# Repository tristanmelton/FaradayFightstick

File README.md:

### FaradayFightstick
Utilize Hall Effect sensors in an open-source leverless.

Use an ATMEGA microcontroller to read the analog out from the hall effect sensor located on the opposite side of the PCB from the switch. Then, the ATMEGA will act as the switch and output high or low to a Brooks board for each button press.

There are board versions for a RP2040, Brooks P5 Mini and Brooks Gen-5X Mini. I have tested the RP2040 and P5 Mini versions and they both work on PC.
## Setup
The board is relatively simple to set up - the most difficult part was soldering the USB-C for the ATMEGA32u4. I have no reflow oven so I used my conventional oven with solder paste, which works but is a little difficult to get the timing right to not melt the plastic in the connector.

Once all components are soldered, burn the Arduino bootloader with the "Arduino as ISP" option with an Arduino Uno or equivalent, or another bootloader burner, connected to the ICSP headers on the ATMEGA32u4 which are broken out for convenience, set to an Arduino Micro as the target. Then, plug in the USB-C and upload the ADC.ino sketch.

Once uploaded, unplug and hold LP while plugging back in and run the configurator python script (to be wrapped into an exe later). It should automatically detect the controller. If not, select the COM port corresponding to your board (should say COMXX: Arduino Micro), and click Connect. The progress bar will fill as the default values are read from memory. Set the values using the sliders and click "Submit New Thresholds". Wait for the progress bar to fill and then you can unplug.

Unplug from the ATMEGA side and plug the controller into your computer. If using the RP2040 board, upload the GP2040-CE firmware. Once done, you should be good to go!

There is compatibility for a MagicBoots with the RP2040 board but I have not tested it nor the P5 mini or Gen-5X versions as I don't own a PS5. Always open to donations :)
## TODO
- [ ] Test the P5 Mini version on a PS5.
- [x] Add an "unpressed" level so users have an idea of what range of value to put in
- [x] Add a diode on the voltage input from each USB socket to prevent backflow of current to the host PC and damaging it

## Changelog
# v1.1 (5/5/2025)
- Added boards for P5 mini and Gen-5X mini
- Added current-blocking diodes to prevent blowing up your USB if plugged into both USB ports at the same time
- Updated ADC firmware to support additional commands:
  - GETALLVAL;: get all current button values.
  - GETALLTRIG;: get all trigger threshold levels.
  - GETTRIG;XX: get a singular trigger threshold from memory.  XX indicates the memory offset to read from.
  - LP;X, MP;X, HP;X, SHP;X,...: Sets the trigger threshold value to X in absolute units.
- Updated interface software to use sliders from 100 to 0 to set the sensitivity. 100 is max sensitivity, 0 is no sensitivity.
- Software will try and auto-detect the controller when plugged in. 
# v1.0 (3/6/2025)
The leverless is working! I wrote a quick interface with Python to read and write button trigger thresholds to the EEPROM. The system works as an official "1.0"!

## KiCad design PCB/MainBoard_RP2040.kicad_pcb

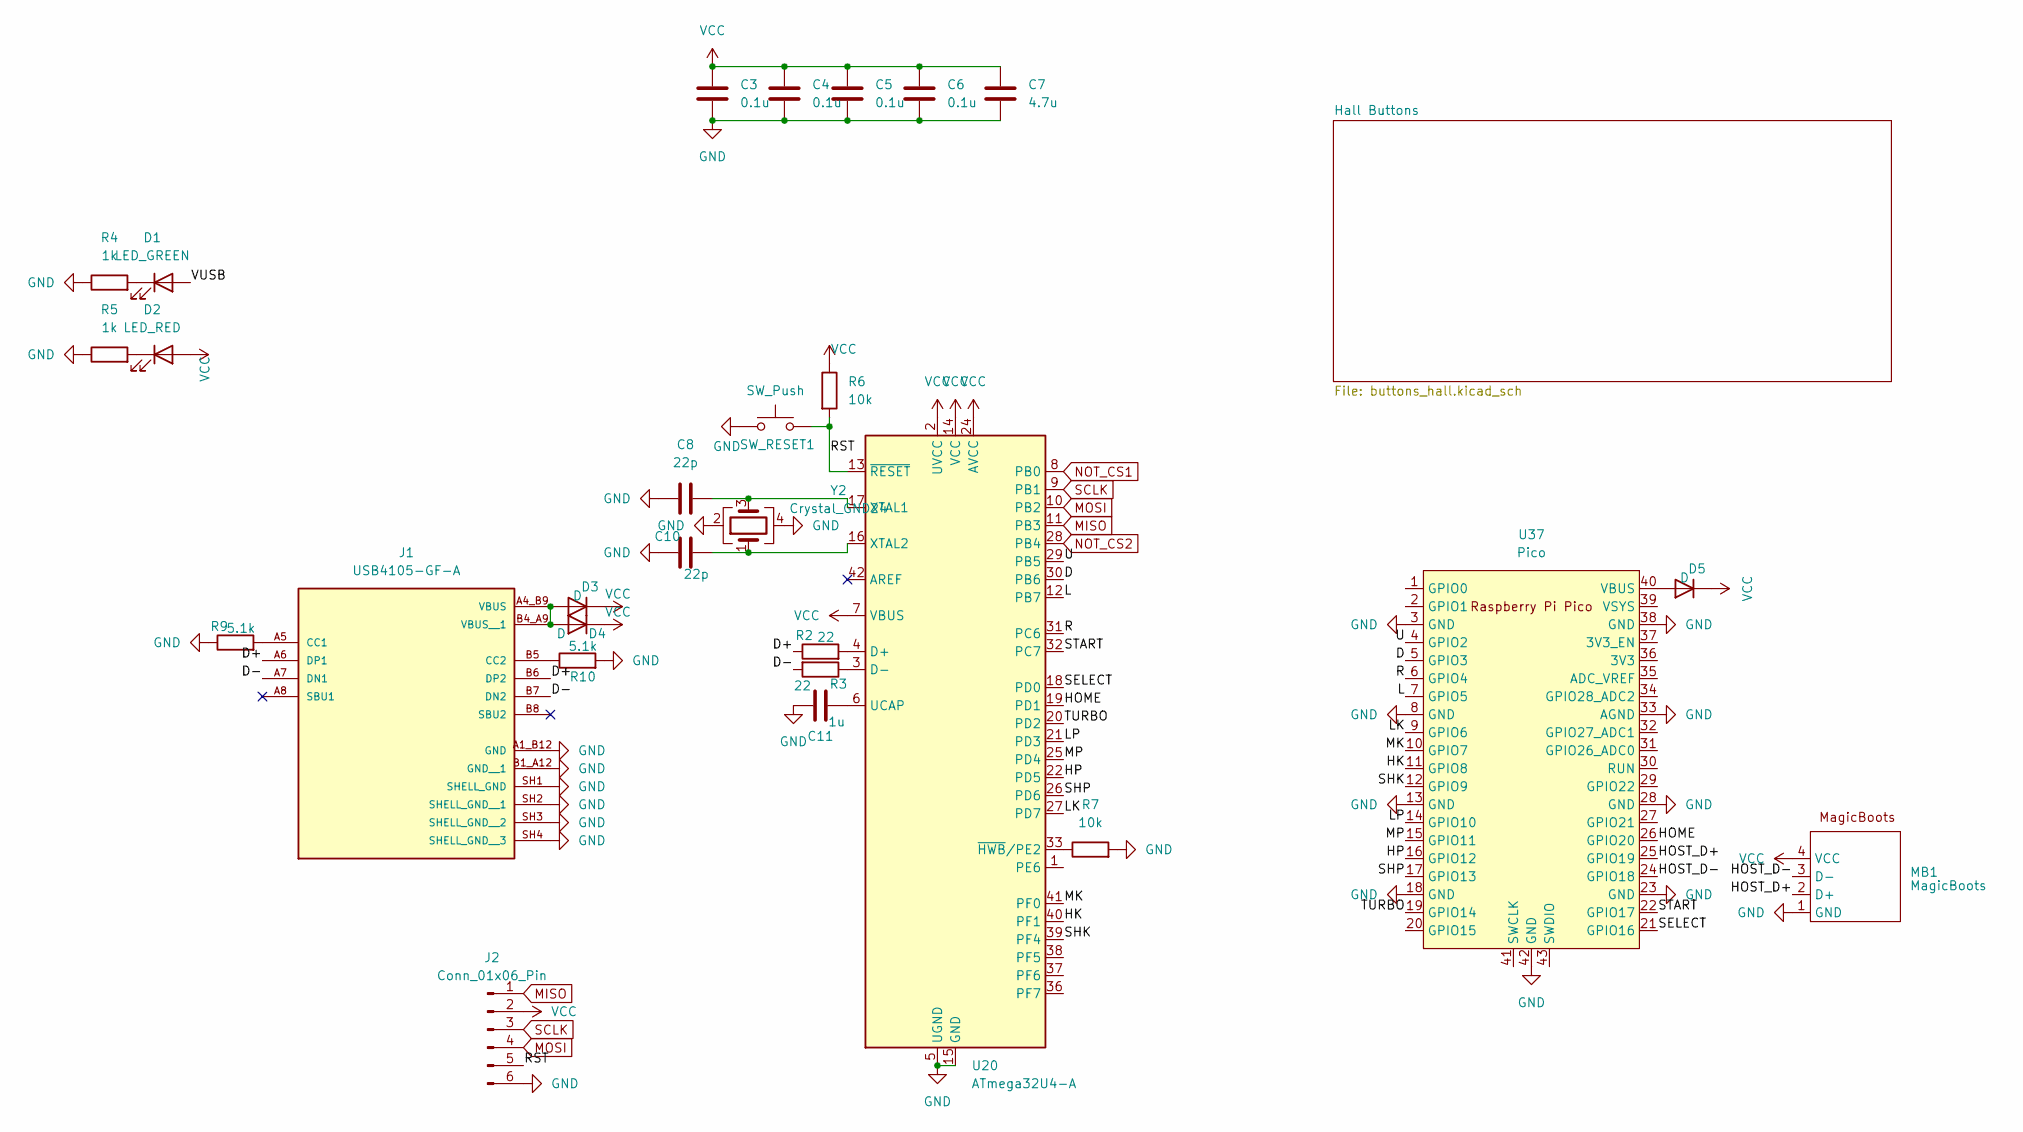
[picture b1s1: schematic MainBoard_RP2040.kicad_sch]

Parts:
C3, C4, C5, C6: 0.1u; C_0603_1608Metric
C7: 4.7u; C_0603_1608Metric
C8, C10: 22p; C_0603_1608Metric
C11: 1u; C_0603_1608Metric
D1: LED_GREEN; LED_0201_0603Metric
D2: LED_RED; LED_0201_0603Metric
D3, D4, D5: D; D_0603_1608Metric
J1: USB4105-GF-A; GCT_USB4105-GF-A; PARTREV B4
J2: Conn_01x06_Pin; PinHeader_2x03_P2.54mm_Vertical
MB1: MagicBoots
R2, R3: 22; R_0603_1608Metric
R4, R5: 1k; R_0603_1608Metric
R6, R7: 10k; R_0603_1608Metric
R9, R10: 5.1k; R_0603_1608Metric
SW_RESET1: SW_Push; SW_SPST_TL3342
U20: ATmega32U4-A; TQFP-44_10x10mm_P0.8mm
U37: Pico; RPi_Pico_SMD_TH
Y2: Crystal_GND24; Crystal_SMD_SeikoEpson_FA238-4Pin_3.2x2.5mm

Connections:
/D: U20.30 (PB6), U37.5 (GPIO3)
/D+: J1.A6 (DP1), J1.B6 (DP2), R2.1
/D-: J1.A7 (DN1), J1.B7 (DN2), R3.2
/HK: U20.40 (PF1), U37.11 (GPIO8)
/HOME: U20.19 (PD1), U37.26 (GPIO20)
/HOST_D+: MB1.2 (D+), U37.25 (GPIO19)
/HOST_D-: MB1.3 (D-), U37.24 (GPIO18)
/HP: U20.22 (PD5), U37.16 (GPIO12)
/L: U20.12 (PB7), U37.7 (GPIO5)
/LK: U20.27 (PD7), U37.9 (GPIO6)
/LP: U20.21 (PD3), U37.14 (GPIO10)
/MK: U20.41 (PF0), U37.10 (GPIO7)
/MP: U20.25 (PD4), U37.15 (GPIO11)
/R: U20.31 (PC6), U37.6 (GPIO4)
/RST: J2.5, R6.2, SW_RESET1.2, U20.13 (~RESET)
/SELECT: U20.18 (PD0), U37.21 (GPIO16)
/SHK: U20.39 (PF4), U37.12 (GPIO9)
/SHP: U20.26 (PD6), U37.17 (GPIO13)
/START: U20.32 (PC7), U37.22 (GPIO17)
/TURBO: U20.20 (PD2), U37.19 (GPIO14)
/U: U20.29 (PB5), U37.4 (GPIO2)
GND: C3.2, C4.2, C5.2, C6.2, C7.2, C8.1, C10.1, C11.1, J1.A1_B12 (GND), J1.B1_A12 (GND__1), J1.SH1 (SHELL_GND), J1.SH2 (SHELL_GND__1), J1.SH3 (SHELL_GND__2), J1.SH4 (SHELL_GND__3), J2.6, MB1.1 (GND), R4.1, R5.1, R7.2, R9.1, R10.2, SW_RESET1.1, U20.5 (UGND), U20.15 (GND), U20.23 (GND), U20.35 (GND), U20.43 (GND), U37.3 (GND), U37.8 (GND), U37.13 (GND), U37.18 (GND), U37.23 (GND), U37.28 (GND), U37.33 (AGND), U37.38 (GND), U37.42 (GND), Y2.2, Y2.4; also elsewhere on the board
MISO: J2.1, U20.11 (PB3); also elsewhere on the board
MOSI: J2.4, U20.10 (PB2); also elsewhere on the board
NOT_CS1: U20.8 (PB0); also elsewhere on the board
NOT_CS2: U20.28 (PB4); also elsewhere on the board
unnamed: D1.1 (K), R4.2
unnamed: D2.1 (K), R5.2
unnamed: D3.2 (A), D4.2 (A), J1.A4_B9 (VBUS), J1.B4_A9 (VBUS__1)
unnamed: D5.2 (A), U37.40 (VBUS)
unnamed: J1.A5 (CC1), R9.2
unnamed: J1.B5 (CC2), R10.1
unnamed: R2.2, U20.4 (D+)
unnamed: R3.1, U20.3 (D-)
unnamed: C11.2, U20.6 (UCAP)
unnamed: C8.2, U20.17 (XTAL1), Y2.3
unnamed: C10.2, U20.16 (XTAL2), Y2.1
unnamed: R7.1, U20.33 (~HWB/PE2)
SCLK: J2.3, U20.9 (PB1); also elsewhere on the board
VCC: C3.1, C4.1, C5.1, C6.1, C7.1, D2.2 (A), D3.1 (K), D4.1 (K), D5.1 (K), J2.2, MB1.4 (VCC), R6.1, U20.2 (UVCC), U20.7 (VBUS), U20.14 (VCC), U20.24 (AVCC), U20.34 (VCC), U20.44 (AVCC); also elsewhere on the board

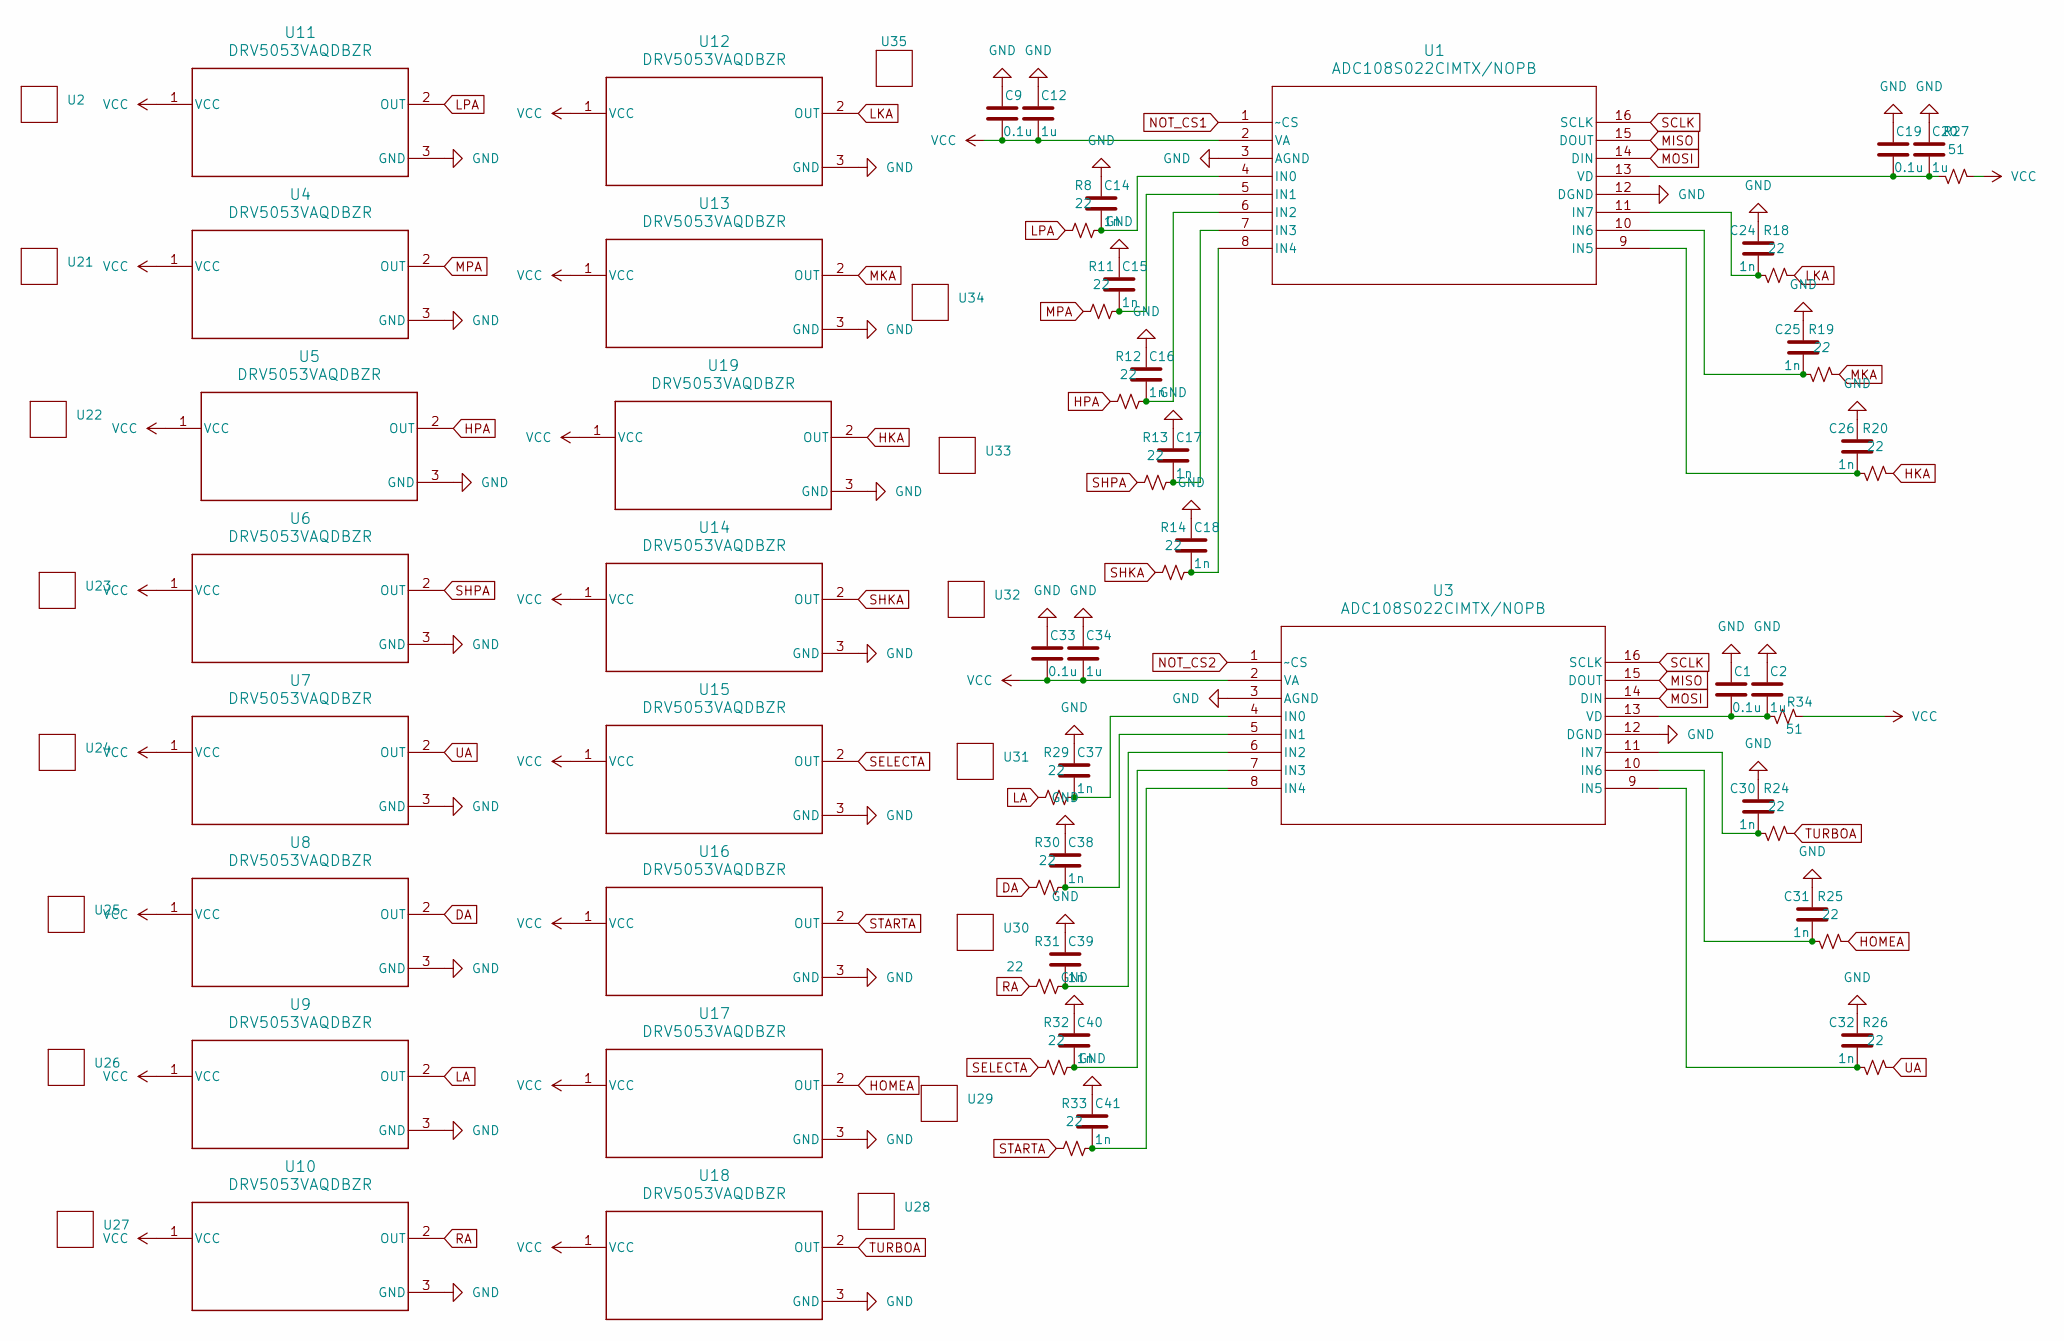
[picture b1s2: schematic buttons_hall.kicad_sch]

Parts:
C1, C9, C19, C33: 0.1u; C_0603_1608Metric
C2, C12, C20, C34: 1u; C_0603_1608Metric
C14, C15, C16, C17, C18, C24, C25, C26, C30, C31, C32, C37, C38, C39, C40, C41: 1n; C_0603_1608Metric
R8, R11, R12, R13, R14, R18, R19, R20, R24, R25, R26, R29, R30, R31, R32, R33: 22; R_0603_1608Metric
R27, R34: 51; R_0603_1608Metric
U1, U3: ADC108S022CIMTX/NOPB; MTC16
U2, U21, U22, U23, U24, U25, U26, U27, U28, U29, U30, U31, U32, U33, U34, U35: Gateron Jade Pro Magnetic
U4, U5, U6, U7, U8, U9, U10, U11, U12, U13, U14, U15, U16, U17, U18, U19: DRV5053VAQDBZR; DBZ0003A_N

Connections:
DA: R30.1, U8.2 (OUT)
GND: C1.1, C2.1, C9.1, C12.1, C14.1, C15.1, C16.1, C17.1, C18.1, C19.1, C20.1, C24.1, C25.1, C26.1, C30.1, C31.1, C32.1, C33.1, C34.1, C37.1, C38.1, C39.1, C40.1, C41.1, U1.3 (AGND), U1.12 (DGND), U3.3 (AGND), U3.12 (DGND), U4.3 (GND), U5.3 (GND), U6.3 (GND), U7.3 (GND), U8.3 (GND), U9.3 (GND), U10.3 (GND), U11.3 (GND), U12.3 (GND), U13.3 (GND), U14.3 (GND), U15.3 (GND), U16.3 (GND), U17.3 (GND), U18.3 (GND), U19.3 (GND); also elsewhere on the board
HKA: R20.1, U19.2 (OUT)
HOMEA: R25.1, U17.2 (OUT)
HPA: R12.1, U5.2 (OUT)
LA: R29.1, U9.2 (OUT)
LKA: R18.1, U12.2 (OUT)
LPA: R8.1, U11.2 (OUT)
MISO: U1.15 (DOUT), U3.15 (DOUT); also elsewhere on the board
MKA: R19.1, U13.2 (OUT)
MOSI: U1.14 (DIN), U3.14 (DIN); also elsewhere on the board
MPA: R11.1, U4.2 (OUT)
NOT_CS1: U1.1 (~CS); also elsewhere on the board
NOT_CS2: U3.1 (~CS); also elsewhere on the board
unnamed: C14.2, R8.2, U1.4 (IN0)
unnamed: C15.2, R11.2, U1.5 (IN1)
unnamed: C16.2, R12.2, U1.6 (IN2)
unnamed: C17.2, R13.2, U1.7 (IN3)
unnamed: C18.2, R14.2, U1.8 (IN4)
unnamed: C26.2, R20.2, U1.9 (IN5)
unnamed: C25.2, R19.2, U1.10 (IN6)
unnamed: C24.2, R18.2, U1.11 (IN7)
unnamed: C19.2, C20.2, R27.2, U1.13 (VD)
unnamed: C37.2, R29.2, U3.4 (IN0)
unnamed: C38.2, R30.2, U3.5 (IN1)
unnamed: C39.2, R31.2, U3.6 (IN2)
unnamed: C40.2, R32.2, U3.7 (IN3)
unnamed: C41.2, R33.2, U3.8 (IN4)
unnamed: C32.2, R26.2, U3.9 (IN5)
unnamed: C31.2, R25.2, U3.10 (IN6)
unnamed: C30.2, R24.2, U3.11 (IN7)
unnamed: C1.2, C2.2, R34.2, U3.13 (VD)
RA: R31.1, U10.2 (OUT)
SCLK: U1.16 (SCLK), U3.16 (SCLK); also elsewhere on the board
SELECTA: R32.1, U15.2 (OUT)
SHKA: R14.1, U14.2 (OUT)
SHPA: R13.1, U6.2 (OUT)
STARTA: R33.1, U16.2 (OUT)
TURBOA: R24.1, U18.2 (OUT)
UA: R26.1, U7.2 (OUT)
VCC: C9.2, C12.2, C33.2, C34.2, R27.1, R34.1, U1.2 (VA), U3.2 (VA), U4.1 (VCC), U5.1 (VCC), U6.1 (VCC), U7.1 (VCC), U8.1 (VCC), U9.1 (VCC), U10.1 (VCC), U11.1 (VCC), U12.1 (VCC), U13.1 (VCC), U14.1 (VCC), U15.1 (VCC), U16.1 (VCC), U17.1 (VCC), U18.1 (VCC), U19.1 (VCC); also elsewhere on the board

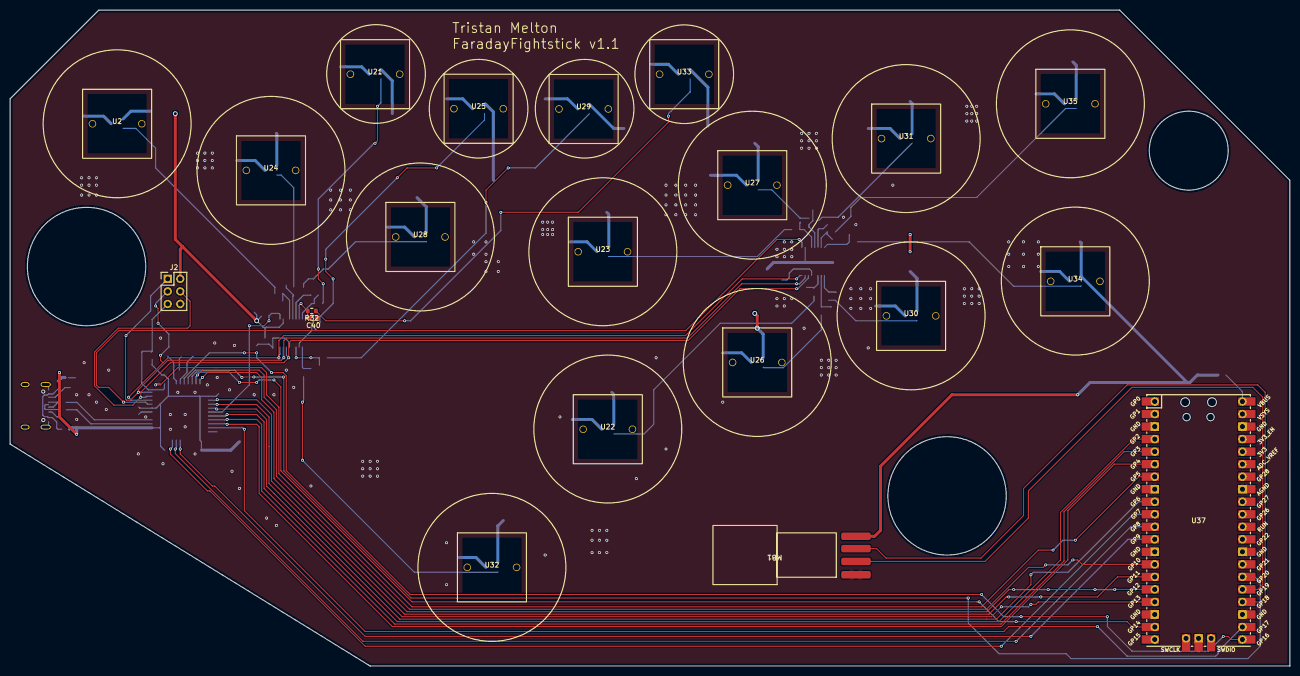
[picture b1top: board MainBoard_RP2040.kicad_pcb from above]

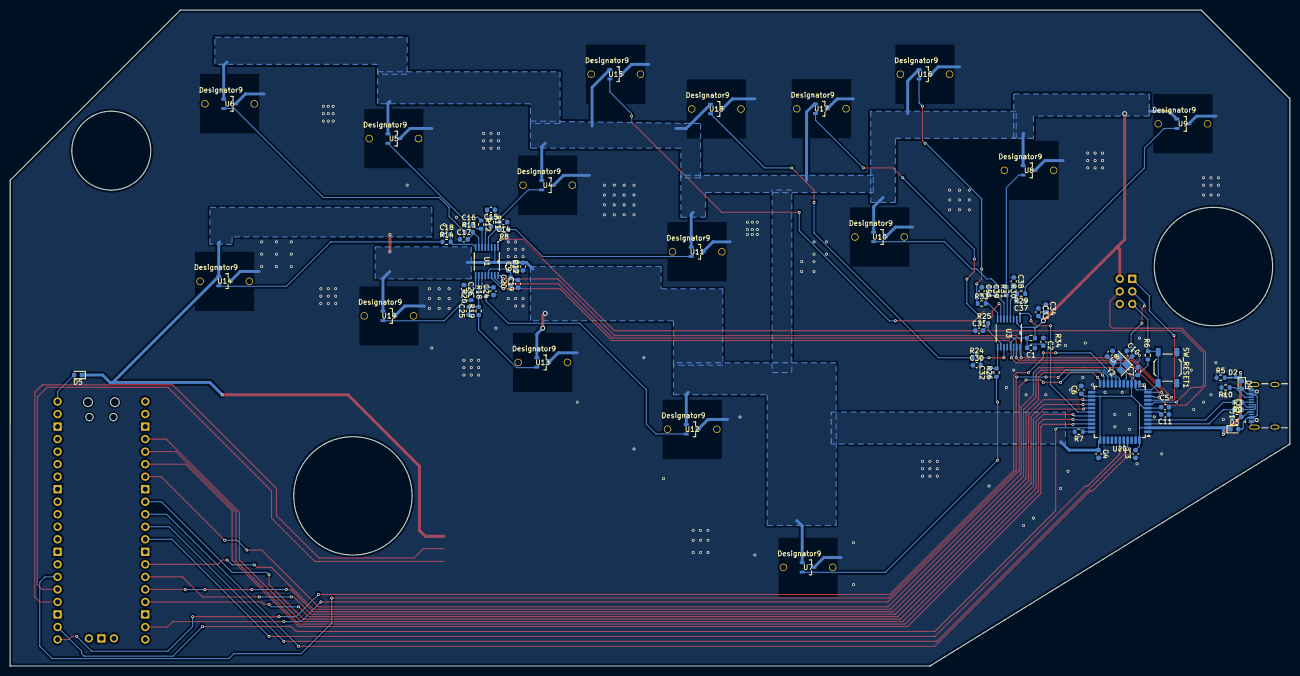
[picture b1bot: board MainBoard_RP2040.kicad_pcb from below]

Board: 2 copper layers, 259.5 x 133.0 mm, 102 parts (81 on the bottom side), 73 nets.

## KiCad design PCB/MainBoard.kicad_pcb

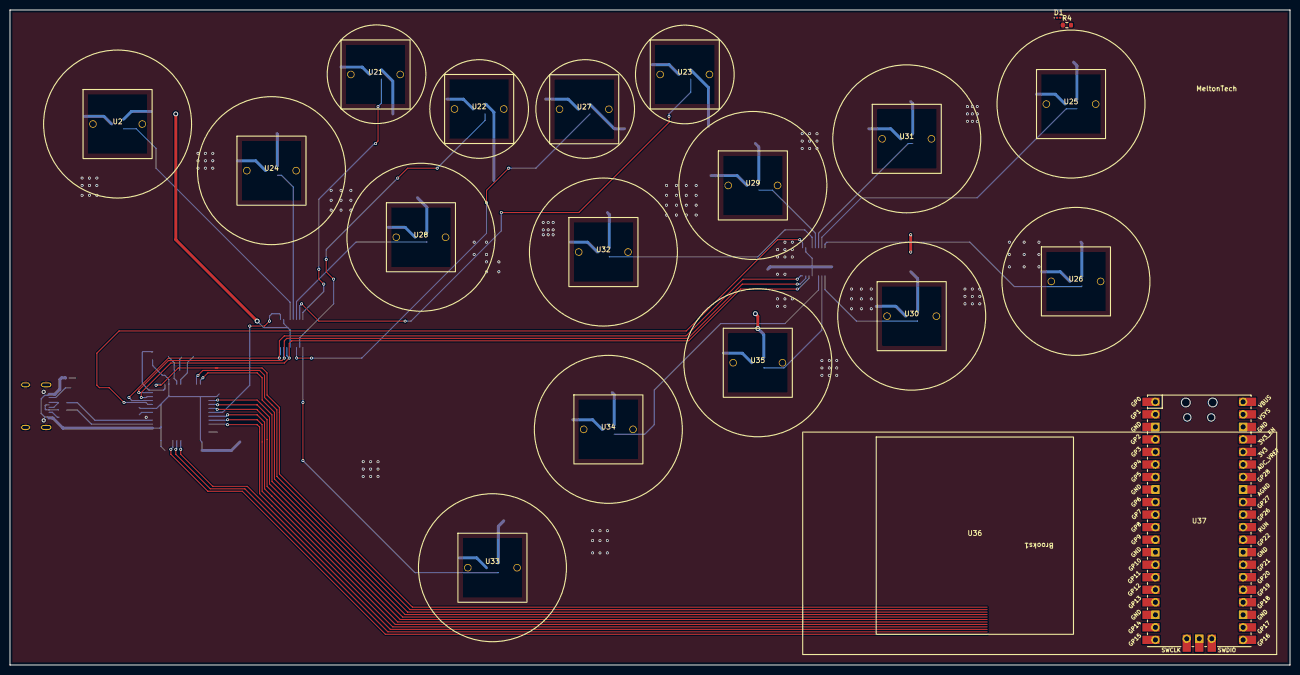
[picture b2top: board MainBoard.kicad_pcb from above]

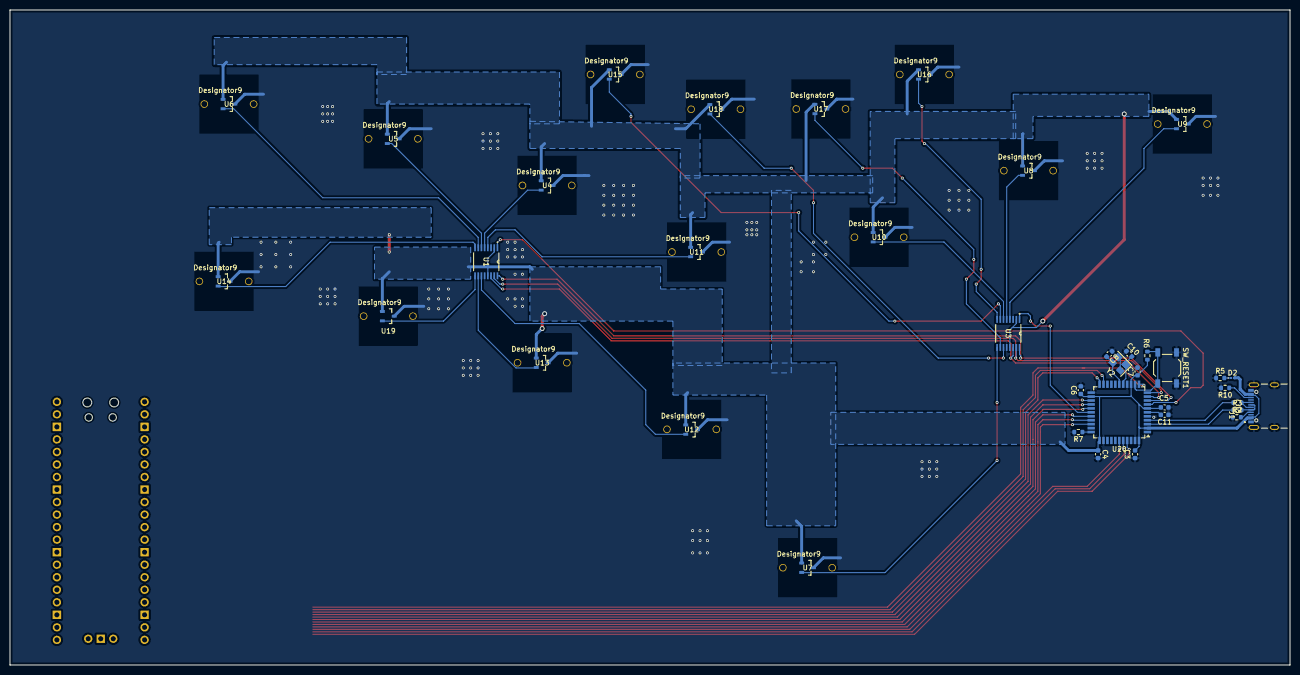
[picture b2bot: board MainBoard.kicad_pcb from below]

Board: 2 copper layers, 259.5 x 132.8 mm, 59 parts (38 on the bottom side), 36 nets.

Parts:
Brooks1: BrooksP5Plus
C3, C4, C5, C6: 0.1u; C_0603_1608Metric
C7: 4.7u; C_0603_1608Metric
C8, C10: 22p; C_0603_1608Metric
C11: 1u; C_0603_1608Metric
D1: LED_GREEN; LED_0201_0603Metric
D2: LED_RED; LED_0201_0603Metric
J1: USB4105-GF-A; GCT_USB4105-GF-A
R2, R3: 22; R_0603_1608Metric
R4, R5: 1k; R_0603_1608Metric
R6, R7: 10k; R_0603_1608Metric
R9, R10: 5.1k; R_0603_1608Metric
SW_RESET1: SW_Push; SW_SPST_TL3342
U1, U3: ADC108S022CIMTX/NOPB; MTC16
U2, U21, U22, U23, U24, U25, U26, U27, U28, U29, U30, U31, U32, U33, U34, U35: Gateron Jade Pro Magnetic
U4, U5, U6, U7, U8, U9, U10, U11, U12, U13, U14, U15, U16, U17, U18, U19: DRV5053VAQDBZR; DBZ0003A_N
U20: ATmega32U4-A; TQFP-44_10x10mm_P0.8mm
U36: BrooksP5Mini
U37: Pico; RPi_Pico_SMD_TH
Y2: Crystal_GND24; Crystal_SMD_SeikoEpson_FA238-4Pin_3.2x2.5mm

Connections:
/D+: J1.A6 (DP1), J1.B6 (DP2), R2.1
/D-: J1.A7 (DN1), J1.B7 (DN2), R3.2
DA: U3.5 (IN1), U8.2 (OUT)
GND: C3.2, C4.2, C5.2, C6.2, C7.2, C8.1, C10.1, C11.1, J1.A1_B12 (GND), J1.B1_A12 (GND__1), J1.SH1 (SHELL_GND), J1.SH2 (SHELL_GND__1), J1.SH3 (SHELL_GND__2), J1.SH4 (SHELL_GND__3), R4.1, R5.1, R7.2, R9.1, R10.2, SW_RESET1.1, U1.3 (AGND), U1.12 (DGND), U3.3 (AGND), U3.12 (DGND), U4.3 (GND), U5.3 (GND), U6.3 (GND), U7.3 (GND), U8.3 (GND), U9.3 (GND), U10.3 (GND), U11.3 (GND), U12.3 (GND), U13.3 (GND), U14.3 (GND), U15.3 (GND), U16.3 (GND), U17.3 (GND), U18.3 (GND), U19.3 (GND), U20.5 (UGND), U20.15 (GND), U20.23 (GND), U20.35 (GND), U20.43 (GND), Y2.2, Y2.4
HKA: U1.9 (IN5), U19.2 (OUT)
HOMEA: U3.10 (IN6), U17.2 (OUT)
HPA: U1.6 (IN2), U5.2 (OUT)
LA: U3.4 (IN0), U9.2 (OUT)
LKA: U1.11 (IN7), U12.2 (OUT)
LPA: U1.4 (IN0), U11.2 (OUT)
MISO: U1.15 (DOUT), U3.15 (DOUT), U20.11 (PB3)
MKA: U1.10 (IN6), U13.2 (OUT)
MOSI: U1.14 (DIN), U3.14 (DIN), U20.10 (PB2)
MPA: U1.5 (IN1), U4.2 (OUT)
NOT_CS1: U1.1 (~CS), U20.8 (PB0)
NOT_CS2: U3.1 (~CS), U20.28 (PB4)
unnamed: D1.1 (K), R4.2
unnamed: D2.1 (K), R5.2
unnamed: J1.A5 (CC1), R9.2
unnamed: J1.B5 (CC2), R10.1
unnamed: R2.2, U20.4 (D+)
unnamed: R3.1, U20.3 (D-)
unnamed: C11.2, U20.6 (UCAP)
unnamed: C8.2, U20.17 (XTAL1), Y2.3
unnamed: C10.2, U20.16 (XTAL2), Y2.1
unnamed: R7.1, U20.33 (~HWB/PE2)
unnamed: R6.2, SW_RESET1.2, U20.13 (~RESET)
RA: U3.6 (IN2), U10.2 (OUT)
SCLK: U1.16 (SCLK), U3.16 (SCLK), U20.9 (PB1)
SELECTA: U3.7 (IN3), U15.2 (OUT)
SHKA: U1.8 (IN4), U14.2 (OUT)
SHPA: U1.7 (IN3), U6.2 (OUT)
STARTA: U3.8 (IN4), U16.2 (OUT)
TURBOA: U3.11 (IN7), U18.2 (OUT)
UA: U3.9 (IN5), U7.2 (OUT)
VCC: C3.1, C4.1, C5.1, C6.1, C7.1, D2.2 (A), J1.A4_B9 (VBUS), J1.B4_A9 (VBUS__1), R6.1, U1.2 (VA), U1.13 (VD), U3.2 (VA), U3.13 (VD), U4.1 (VCC), U5.1 (VCC), U6.1 (VCC), U7.1 (VCC), U8.1 (VCC), U9.1 (VCC), U10.1 (VCC), U11.1 (VCC), U12.1 (VCC), U13.1 (VCC), U14.1 (VCC), U15.1 (VCC), U16.1 (VCC), U17.1 (VCC), U18.1 (VCC), U19.1 (VCC), U20.2 (UVCC), U20.7 (VBUS), U20.14 (VCC), U20.24 (AVCC), U20.34 (VCC), U20.44 (AVCC)

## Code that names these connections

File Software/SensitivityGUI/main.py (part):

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label_hp = Label(frame_buttonconfig, text="HP").grid(row=1, column=4)
slider_hp = Scale(frame_buttonconfig, from_=100, to=0)
slider_hp.grid(row=1,column=5)
label_shp = Label(frame_buttonconfig, text="SHP").grid(row=1, column=6)
slider_shp = Scale(frame_buttonconfig, from_=100, to=0)
slider_shp.grid(row=1,column=7)

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label_hk = Label(frame_buttonconfig, text="HK").grid(row=2, column=4)
slider_hk = Scale(frame_buttonconfig, from_=100, to=0)
slider_hk.grid(row=2,column=5)
label_shk = Label(frame_buttonconfig, text="SHK").grid(row=2, column=6)
slider_shk = Scale(frame_buttonconfig, from_=100, to=0)
slider_shk.grid(row=2,column=7)

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label_select = Label(frame_buttonconfig, text = "SELECT").grid(row=4, column=2)
slider_select = Scale(frame_buttonconfig, from_=100, to=0)
slider_select.grid(row=4,column=3)
label_turbo = Label(frame_buttonconfig, text="TURBO").grid(row=4, column=4)
slider_turbo = Scale(frame_buttonconfig, from_=100, to=0)
slider_turbo.grid(row=4,column=5)
label_home = Label(frame_buttonconfig, text="HOME").grid(row=4, column=6)
slider_home = Scale(frame_buttonconfig, from_=100, to=0)
slider_home.grid(row=4,column=7)

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
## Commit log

2025-01-27 Added first pass of PCB for collecting initial components for the MCU.
2025-01-30 Updated board with the right hall effect analog sensor and some ADCs. Considering reducing the MCU.
2025-01-31 Worked on schematic, added USB-C, worked on pcb
2025-01-31 Updated README with today's progress
2025-02-04 Updated PCB and schematic with the Gateron footprint, added dummy Brooks footprint
2025-02-10 Fallback Pico GP2040-CE added
2025-02-10 Removed other controller boards from RP2040
2025-02-10 Added Gitignore
2025-02-10 Fixed Gitignore
2025-03-02 Confirmed working, moving towards PCB v1.1
2025-03-07 Version 1.0 Commit
2025-03-07 Adding progress bars to GUI
2025-03-08 Added Progress Bar
2025-03-10 Create LICENSE
2025-04-05 Added the additional components to support the ADCs
2025-04-05 Working on layout of PCB to include the other components....
2025-04-08 PCB Updated to include the ADC improved components
2025-05-06 Added Gen5X and P5Mini versions. Updated the firmware to support new get all threshold and get all current level commands. Updated the user software to use draggable bars that scale t100% for highest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
2025-05-06 Added protective diodes to RP2040 Board
2025-05-06 Update gitignore
